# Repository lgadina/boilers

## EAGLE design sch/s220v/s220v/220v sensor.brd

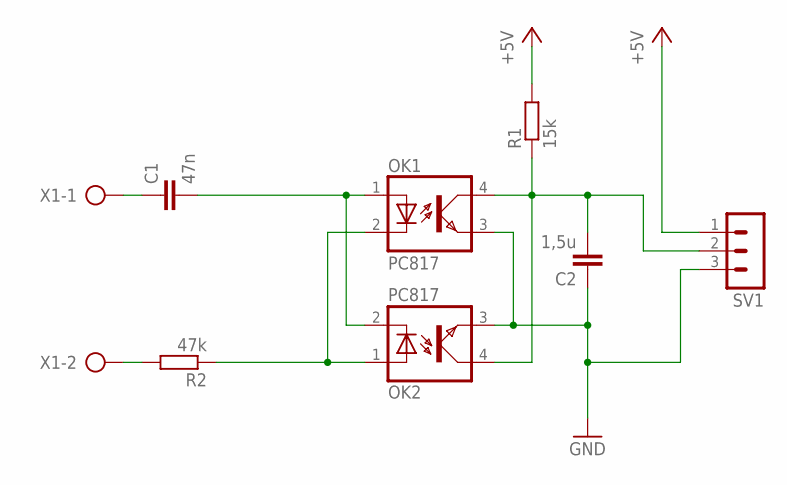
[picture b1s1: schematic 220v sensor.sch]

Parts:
C1: 47n; C075-032X103
C2: 1,5u; C075-032X103
OK1, OK2: PC817; DIL04
R1: 15k; 0207/15
R2: 47k; 0207/15
SV1: MA03-1
X1: AK300/2

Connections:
+5V: R1.2, SV1.1
GND: C2.1, OK1.3 (EMIT), OK2.3 (EMIT), SV1.3
unnamed: OK1.2 (C), OK2.1 (A), R2.1
unnamed: C1.2, OK1.1 (A), OK2.2 (C)
unnamed: R2.2, X1.2
unnamed: C1.1, X1.1
unnamed: C2.2, OK1.4 (COL), OK2.4 (COL), R1.1, SV1.2

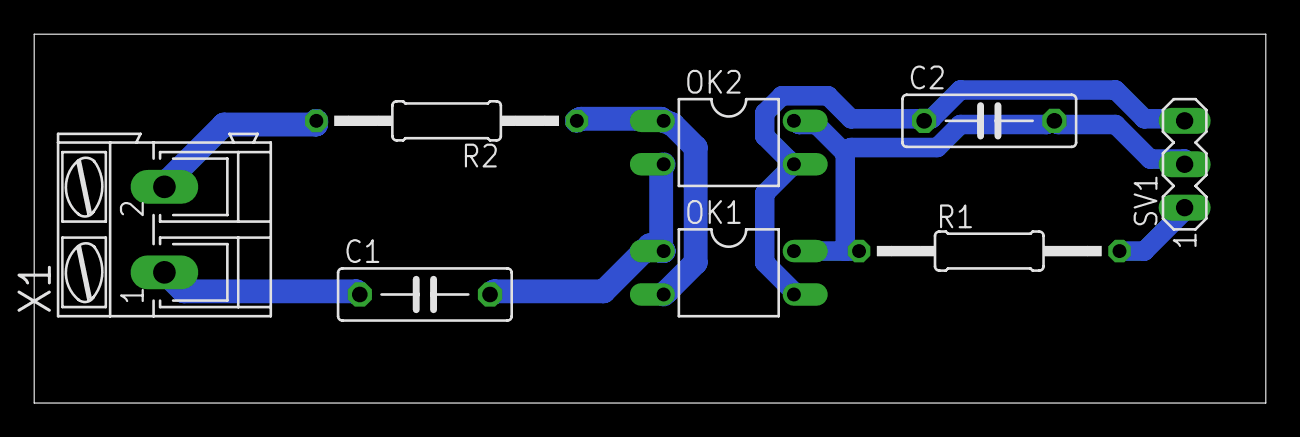
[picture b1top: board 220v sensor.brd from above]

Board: 2 copper layers, 72.1 x 21.6 mm, 8 parts (0 on the bottom side), 7 nets.
